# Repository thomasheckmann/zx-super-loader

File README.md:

# zx-super-loader
DIY construction from danish magazine Ny Elektronik 1985 to improve loading from tape for ZX Spectrum, ZX81 &amp; Lambda computers.

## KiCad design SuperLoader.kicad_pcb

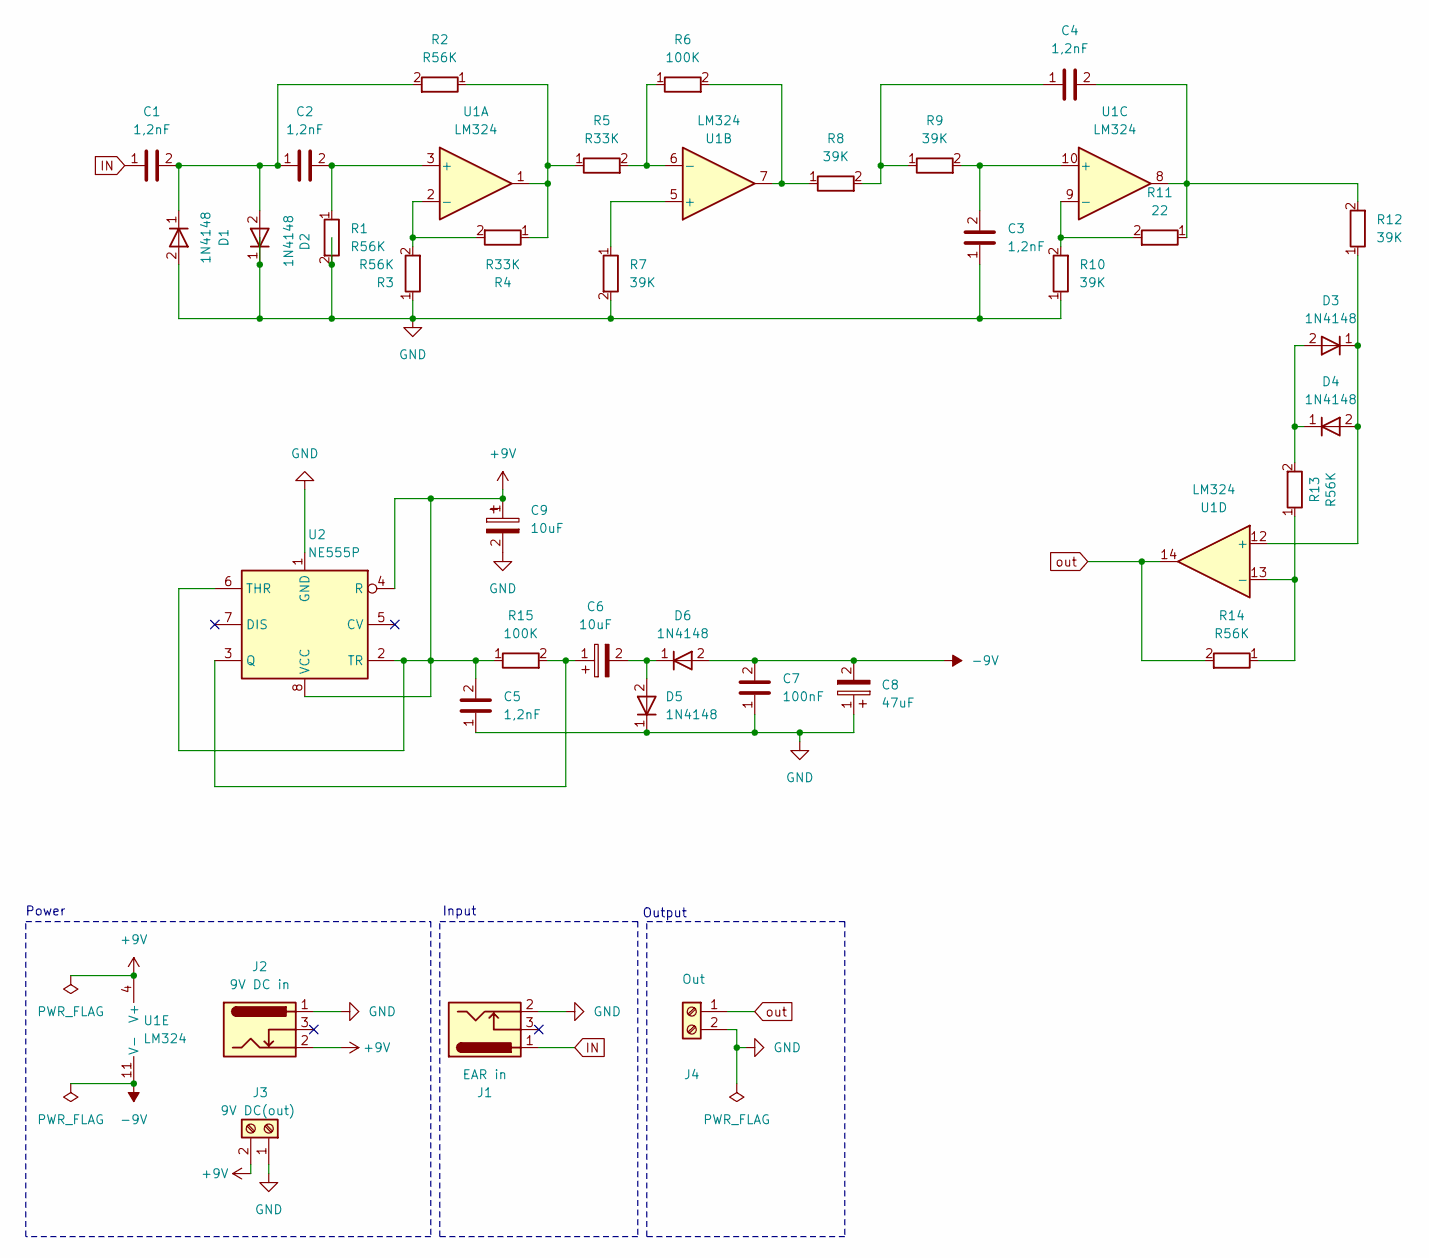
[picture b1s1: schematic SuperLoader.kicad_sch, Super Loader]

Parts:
C1, C2, C3, C4, C5: 1,2nF; C_Disc_D4.3mm_W1.9mm_P5.00mm
C6, C9: 10uF; CP_Radial_D4.0mm_P1.50mm
C7: 100nF; C_Disc_D4.3mm_W1.9mm_P5.00mm
C8: 47uF; CP_Radial_D4.0mm_P1.50mm
D1, D2, D3, D4, D5, D6: 1N4148; D_DO-35_SOD27_P10.16mm_Horizontal
J1: EAR in; 3.5mm mono jack chassis with switch
J2: 9V DC in; BarrelJack_GCT_DCJ200-10-A_Horizontal
J3: 9V DC(out); PinHeader_1x02_P2.54mm_Horizontal
J4: Out; PinHeader_1x02_P2.54mm_Horizontal
R1, R2, R3, R13, R14: R56K; R_Axial_DIN0207_L6.3mm_D2.5mm_P10.16mm_Horizontal
R4, R5: R33K; R_Axial_DIN0207_L6.3mm_D2.5mm_P10.16mm_Horizontal
R6, R15: 100K; R_Axial_DIN0207_L6.3mm_D2.5mm_P10.16mm_Horizontal
R7, R8, R9, R10, R12: 39K; R_Axial_DIN0207_L6.3mm_D2.5mm_P10.16mm_Horizontal
R11: 22; R_Axial_DIN0207_L6.3mm_D2.5mm_P10.16mm_Horizontal
U1: LM324; DIP-14_W7.62mm_Socket
U2: NE555P; DIP-8_W7.62mm

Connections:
+9V: C5.2, C9.1, J2.2, J3.2, R15.1, U1.4 (V+), U2.2 (TR), U2.4 (R), U2.6 (THR), U2.8 (VCC)
-9V: C7.2, C8.2, D6.2 (A), U1.11 (V-)
GND: C3.1, C5.1, C7.1, C8.1, C9.2, D1.2 (A), D2.1 (K), D5.1 (K), J1.2, J2.1, J3.1, J4.2, R1.2, R3.1, R7.2, R10.1, U2.1 (GND)
IN: C1.1, J1.1
unnamed: C4.1, R8.2, R9.1
unnamed: C4.2, R11.1, R12.2, U1.8
unnamed: C1.2, C2.1, D1.1 (K), D2.2 (A), R2.2
unnamed: D3.2 (A), D4.1 (K), R13.2
unnamed: D3.1 (K), D4.2 (A), R12.1, U1.12 (+)
unnamed: C6.2, D5.2 (A), D6.1 (K)
unnamed: R2.1, R4.1, R5.1, U1.1
unnamed: R6.2, R8.1, U1.7
unnamed: C2.2, R1.1, U1.3 (+)
unnamed: R3.2, R4.2, U1.2 (-)
unnamed: R7.1, U1.5 (+)
unnamed: R5.2, R6.1, U1.6 (-)
unnamed: C3.2, R9.2, U1.10 (+)
unnamed: R10.2, R11.2, U1.9 (-)
unnamed: R13.1, R14.1, U1.13 (-)
unnamed: C6.1, R15.2, U2.3 (Q)
out: J4.1, R14.2, U1.14

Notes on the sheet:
Power
Input
Output

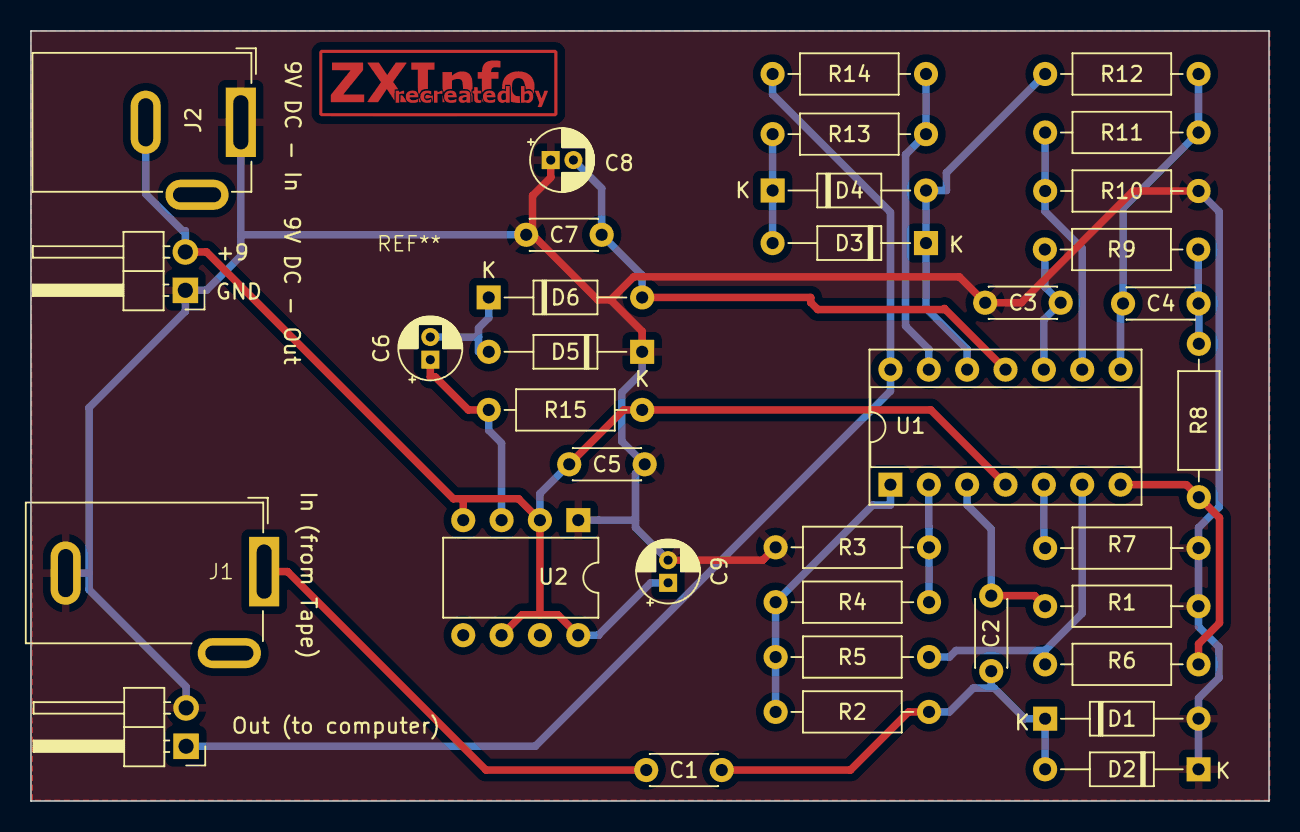
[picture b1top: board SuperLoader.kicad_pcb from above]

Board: 2 copper layers, 82.0 x 51.0 mm, 37 parts (0 on the bottom side), 21 nets.

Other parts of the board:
G200: LOGO; ZXInfo_kicad_logo

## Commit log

2024-03-01 Initial commit V1
2024-03-01 Added copper logo and fixed symbol
